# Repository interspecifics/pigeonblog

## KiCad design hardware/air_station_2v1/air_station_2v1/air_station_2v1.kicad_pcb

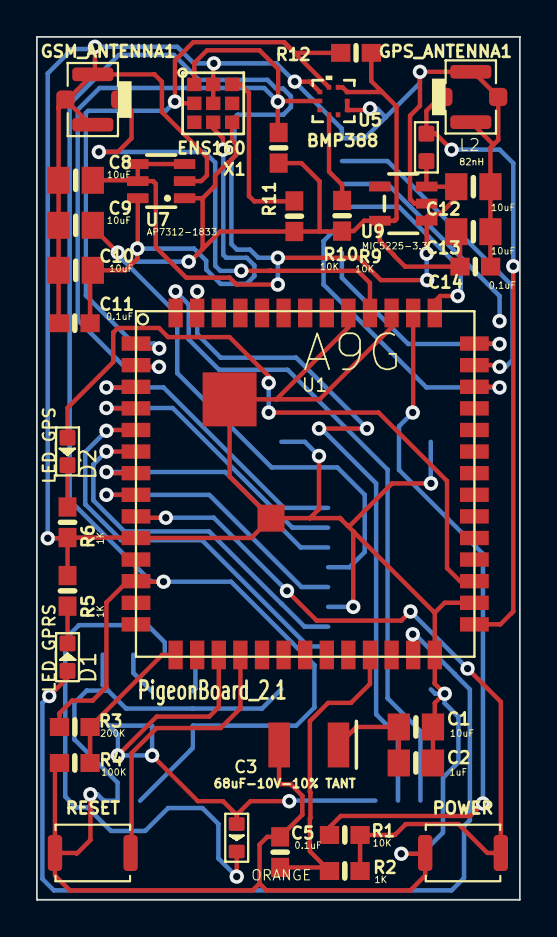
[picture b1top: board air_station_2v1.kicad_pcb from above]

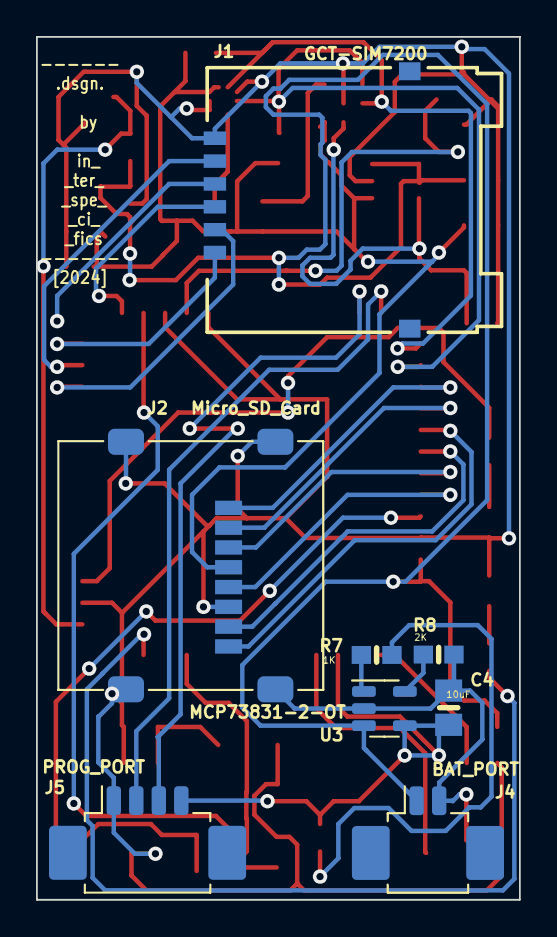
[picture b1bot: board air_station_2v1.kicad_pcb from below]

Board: 2 copper layers, 26.8 x 47.9 mm, 42 parts (8 on the bottom side), 36 nets.

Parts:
C1, C4, C8, C9, C10, C12, C13: 10uF; 0805-NO
C2: 1uF; 0805-NO
C3: 68uF-10V-10% TANT; EIA3528
C5, C11, C14: 0.1uF; 0603-NO
CHG1: ORANGE; D0603
D1: LED_GPRS; LED-0603
D2: LED_GPS; LED-0603
GPS_ANTENNA1: ANTENNA-U-FL; 4P-U-FL
GSM_ANTENNA1: ANTENNA-U-FL; 4P-U-FL
J1: SIM7200-6-0-18-00-X_REVA; GCT_SIM7200-6-0-18-00-X_REVA
J2: Micro_SD_Card; microSD_HC_Molex_47219-2001
J4: BAT_PORT; Molex_PicoBlade_53261-0271_1x02-1MP_P1.25mm_Horizontal
J5: PROG_PORT; Molex_PicoBlade_53261-0471_1x04-1MP_P1.25mm_Horizontal
L2: 82nH; L0603
R1, R9, R10: 10K; 0603-NO
R2, R5, R6, R7: 1K; 0603-NO
R3: 200K; 0603-NO
R4: 100K; 0603-NO
R8: 2K; 0603-NO
R11, R12: 4.7K; 0603-NO
SW_POW1: POWER; SW_Push_SPST_NO_Alps_SKRK
SW_RST1: RESET; SW_Push_SPST_NO_Alps_SKRK
U1: A9G
U3: MCP73831-2-OT; SOT-23-5
U5: BMP388; QFN_BMP388_BOS
U7: AP7312-1833; SOT23-6
U9: MIC5225-3.3; SOT23-5
X1: ENS160

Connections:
1.8V: C10.1, C11.1, U7.6 (VOUT1), X1.4 (VDD)
3.3V: C9.1, C13.1, C14.1, J2.4 (VDD), R9.2, R10.2, R11.2, R12.2, U5.1 (VDDIO), U5.10 (VDD), U7.1 (VOUT2), U9.5 (OUT), X1.5 (VDDIO)
+5V: C4.2, CHG1.+, J5.4, U1.17 (VUSB), U3.4 (V_{DD})
+BATT: C8.1, C12.1, J4.1, L2.2, R3.1, U1.11 (VBAT), U1.12 (VBAT@1), U3.3 (V_{BAT}), U7.3 (EN2), U7.4 (EN1), U7.5 (VIN), U9.1 (IN), U9.3 (EN)
/ADC0: R3.2, R4.1, U1.15 (ADC0)
/GPS_RF: GPS_ANTENNA1.D, L2.1, U1.28 (GPS_RF)
/GSM_RF: GSM_ANTENNA1.D, U1.45 (GPRS_RF)
/I2C2_SCL: R12.1, U1.1 (I2C2_SCL), U5.2 (SCK), X1.2 (SCL/SCK)
/I2C2_SDA: R11.1, U1.2 (I2C2_SDA), U5.4 (SDI), X1.1 (SDA/MOSI)
/IO27: D1.+, U1.26 (IO27)
/IO28: D2.+, U1.30 (IO28)
/IO29: C5.1, R2.1, U1.24 (IO29)
/PWR_KEY: R1.1, R2.2, SW_POW1.1, U1.9 (PWRKEY)
/RESET: SW_RST1.1, U1.18 (RESET)
/SD_CLK: J2.5 (CLK), U1.8 (SD_CLK)
/SD_CMD: J2.3 (CMD), U1.7 (SD_CMD)
/SD_D0: J2.7 (DAT0), U1.6 (SD_D0)
/SD_D1: J2.8 (DAT1), U1.5 (SD_D1)
/SD_D2: J2.2 (DAT3/CD), U1.4 (SD_D2)
/SD_D3: J2.1 (DAT2), U1.3 (SD_D3)
/SIM_CLK: J1.C3 (CLK), U1.41 (SM0_CLK)
/SIM_DATA: J1.C7 (I/O), U1.39 (SM0_DIO)
/SIM_RST: J1.C2 (RST), U1.42 (SM0_RST)
/SIM_VDD: J1.C1 (VCC), U1.40 (VSM0)
/UART_RX: J5.3, U1.53 (UART1_RXD)
/UART_TX: J5.2, U1.54 (UART1_TXD)
/VIN_BAT: C1.2, C2.2, C3.A (+)
/VIO: R1.2, U1.43 (VIO)
GND: C1.1, C2.1, C3.C (-), C4.1, C5.2, C8.2, C9.2, C10.2, C11.2, C12.2, C13.2, C14.2, GPS_ANTENNA1.GND1, GPS_ANTENNA1.GND2, GPS_ANTENNA1.GND3, GSM_ANTENNA1.GND1, GSM_ANTENNA1.GND2, GSM_ANTENNA1.GND3, J1.C5 (GND), J2.6 (VSS), J2.9 (SHIELD), J4.2, J5.1, R4.2, R5.1, R6.1, R8.2, SW_POW1.2, SW_RST1.2, U1.10 (GND), U1.27 (GND@1), U1.29 (GND@2), U1.44 (GND@3), U1.46 (GND@4), U1.55 (GND@5), U1.56 (GND@6), U3.2 (V_{SS}), U5.3 (VSS), U5.8 (VSS), U5.9 (VSS), U7.2 (GND), U9.2 (GND), X1.8 (GND), X1.9 (GND)
unnamed: CHG1.-, R7.1
unnamed: D1.-, R5.2
unnamed: D2.-, R6.2
unnamed: R8.1, U3.5 (PROG)
unnamed: R7.2, U3.1 (STAT)
unnamed: R9.1, U5.6 (CSB)
unnamed: R10.1, X1.7 (~CS)

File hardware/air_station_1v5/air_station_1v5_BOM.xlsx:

|  |  | PigeonBoard v2.0 | Bill of Materials
 |  |  | by Interspecifics | 2023.10.19
Item # | Designator | Qty | Manufacturer | MFR.Part # | Description | Footprint | TYPE |  | Value | Cmp name | JLCPCB Part # | Datasheet
1 | C1, C4, C12, C13 | 4 | TDK | CGA4J1X5R1C106KT0Y0E | 16V 10uF X5R ±10% 0805 Multilayer Ceramic Capacitors MLCC - SMD/SMT ROHS | 0805-NO | SMD |  | 10uF | CAP_CERAMIC0805-NOOUTLINE | C342712 | https://datasheet.lcsc.com/lcsc/2304140030_TDK-CGA4J1X5R1C10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
2 | C2 | 1 | Vishay Intertech | VJ0805Y105KXQTW1BC | 10V 1uF X7R ±10% 0805 Multilayer Ceramic Capacitors MLCC - SMD/SMT ROHS | 0805-NO | SMD |  | 1uF | CAP_CERAMIC0805-NOOUTLINE | C511417 | https://datasheet.lcsc.com/lcsc/2005201835_Vishay-Intertech-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
3 | C3 | 1 | KEMET | T491B686K006AT | 68uF 10V 1.4Ω@100kHz ±20% CASE-B-3528 Tantalum Capacitors ROHS | EIA3528 | SMD |  | 68uF-POLAR-EIA3528-10V-10%(TANT) | 68UF-POLAR-EIA3528-10V-10%(TANT) | C122284 | https://datasheet.lcsc.com/lcsc/2304140030_KEMET-T491B686K00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
4 | C5,C14 | 2 | Samsung Electro-Mechanics | CL10C101JC8NNNC | 100V 100pF C0G ±5% 0603 Multilayer Ceramic Capacitors MLCC - SMD/SMT ROHS | 0603-NO | SMD |  | 0.1uF | CAP_CERAMIC0603_NO | C296717 | https://datasheet.lcsc.com/lcsc/2304140030_Samsung-Electro-M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
5 | C8, C9, C10 | 3 | TDK | CGA4J1X5R1C106KT0Y0E | 16V 10uF X5R ±10% 0805 Multilayer Ceramic Capacitors MLCC - SMD/SMT ROHS | 0805-NO | SMD |  | 10uF | CAP_CERAMIC0805-NOOUTLINE | C342712 | https://datasheet.lcsc.com/lcsc/2304140030_TDK-CGA4J1X5R1C10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
6 | C11 | 1 | Samsung Electro-Mechanics | CL10C101JC8NNNC | 100V 100pF C0G ±5% 0603 Multilayer Ceramic Capacitors MLCC - SMD/SMT ROHS | 0603-NO | SMD |  | 0.1uF | CAP_CERAMIC0603_NO | C296717 | https://datasheet.lcsc.com/lcsc/2304140030_Samsung-Electro-M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
7 | CHG1 | 1 | Amicc | A-SP192YY3C-A01-4T | 180mcd Colorless transparence -40℃~+85℃ 585.5nm~594.5nm yellow 120° 60mW 0603 L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 | LED-0603 | SMD |  | ORANGE | 007-LED0603 | C5151485 | https://datasheet.lcsc.com/lcsc/2209161630_Amicc-A-SP192YY3C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
8 | D1 | 1 | Amicc | A-SP192YB1C-A01-4T | 360mcd Colorless transparence -40℃~+85℃ 465nm~475nm blue 120° 60mW 0603 Light E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 | LED-0603 | SMD |  | LED_GPRS | LED'0603' | C5151484 | https://datasheet.lcsc.com/lcsc/2209161630_Amicc-A-SP192YB1C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
9 | D2 | 1 | Amicc | A-SP192YB1C-A01-4T | 360mcd Colorless transparence -40℃~+85℃ 465nm~475nm blue 120° 60mW 0603 Light E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 | LED-0603 | SMD |  | LED_GPS | LED'0603' | C5151484 | https://datasheet.lcsc.com/lcsc/2209161630_Amicc-A-SP192YB1C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
10 | GPS_ANTENNA1, GSM_ANTENNA1 | 2 | Shenzhen Kinghelm Elec | KH-IPEX3-2020 | 1 Inner needle IPEX Board Edge 6GHz 1.4mm SMD RF Connectors / Coaxial Connector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 | IPEX RF SMD | SMD |  | ANTENNA-U-FL | ANTENNA-U-FL | C530665 | https://datasheet.lcsc.com/lcsc/2005121133_Shenzhen-Kinghelm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
12 | J1 | 1 | Hanbo Electronic | SMO-1545 | SIM Card Connectors Clamshell Gold plating 1.8mm Deck ROHS | GCT_SIM7200 | SMD |  | SIM7200-6-0-18-00-X_REVA | SIM7200-6-0-18-00-X_REVA | C410354 | https://datasheet.lcsc.com/lcsc/2211111000_Hanbo-Electronic-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
13 | J2 | 1 | XKB Connectivity | XKTF-1307-16 | MicroSD SD Card Connectors SMD, 1.6mm Gold plating Deck Copper Alloy Clamshell 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 | Molex_47219-2001 | SMD |  | Micro_SD_Card | Micro_SD_Card | C2885067 | https://datasheet.lcsc.com/lcsc/2110120730_XKB-Connectivity-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
14 | L2 | 1 | Murata Electronics | LQG18HN82NJ00D | 350mA 82nH ±5% 850mΩ 0603 Inductors (SMD) ROHS | L0603 | SMD |  | 82nH | L'0603' | C98008 | https://datasheet.lcsc.com/lcsc/1810311140_Murata-Electronic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
15 | R1, R9, R10 | 3 | ROHM Semicon | ESR03EZPF1002 | 250mW Thick Film Resistors ±100ppm/℃ ±1% 10kΩ 0603 Chip Resistor - Surface Moun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 | 0603-NO | SMD |  | 10K | RESISTOR_0603_NOOUT | C510087 | https://datasheet.lcsc.com/lcsc/2304140030_ROHM-Semicon-ESR0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
16 | R2, R5, R6, R7 | 4 | PANASONIC | ERJUP3F1001V | 250mW Thick Film Resistors ±100ppm/℃ ±1% 1kΩ 0603 Chip Resistor - Surface Mount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 | 0603-NO | SMD |  | 1K | RESISTOR_0603_NOOUT | C491209 | https://datasheet.lcsc.com/lcsc/2005291533_PANASONIC-ERJUP3F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
17 | R3 | 1 | PANASONIC | ERJPA3J204V | 250mW Thick Film Resistors ±5% ±200ppm/℃ 200kΩ 0603 Chip Resistor - Surface Mou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 | 0603-NO | SMD |  | 200K | RESISTOR_0603_NOOUT | C445854 | https://datasheet.lcsc.com/lcsc/2304140030_PANASONIC-ERJPA3J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
18 | R4 | 1 | PANASONIC | ERJUP3F1003V | 250mW Thick Film Resistors ±100ppm/℃ ±1% 100kΩ 0603 Chip Resistor - Surface Mou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 | 0603-NO | SMD |  | 100K | RESISTOR_0603_NOOUT | C491213 | https://datasheet.lcsc.com/lcsc/2005291533_PANASONIC-ERJUP3F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
19 | R8 | 1 | PANASONIC | ERJPA3J202V | 250mW Thick Film Resistors ±5% ±200ppm/℃ 2kΩ 0603 Chip Resistor - Surface Mount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 | 0603-NO | SMD |  | 2K | RESISTOR_0603_NOOUT | C445827 | https://datasheet.lcsc.com/lcsc/2304140030_PANASONIC-ERJPA3J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
20 | SW_POW1 | 1 | ALPSALPINE | SKRKAGE020 | 50mA Brick nogging SPST 12V SMD,2.9x3.9mm Tactile Switches ROHS | SMD,2.9x3.9mm | SMD |  | POWER | SW_Push | C262416 | https://datasheet.lcsc.com/lcsc/1808101152_ALPSALPINE-SKRKAG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
21 | SW_RST1 | 1 | ALPSALPINE | SKRKAGE020 | 50mA Brick nogging SPST 12V SMD,2.9x3.9mm Tactile Switches ROHS | SMD,2.9x3.9mm | SMD |  | RESET | SW_Push | C262416 | https://datasheet.lcsc.com/lcsc/1808101152_ALPSALPINE-SKRKAG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
22 | U1 | 1 | Ai-Thinker | A9G | A9G GPRS/GSM+GPS/BDS Module | AG, SMD, 18.8x19.2mm | SMD |  | A9G | A9G | C133738 | https://docs.ai-thinker.com/_media/b101ps01a4_a9g_product_sp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 |  | https://www.aliexpress.com/item/1005005406907721.html?spm=a2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
23 | U3 | 1 | Microchip Tech | MCP73831T-2ATI/OT | Single cell, Li-Ion/Li-Po charge management controller, 4.20V, Tri-State Status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 | SOT23-5 | SMD |  | MCP73831-2-OT | MCP73831-2-OT | C14879 | https://datasheet.lcsc.com/lcsc/2304140030_Microchip-Tech-MC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
24 | U5 | 1 | Bosch Sensortec | BMP388 | Digital pressure Sensor | QFN_BMP388_BOS | BGA/QFP |  | BMP388 | BMP388 | C779278 | https://www.bosch-sensortec.com/media/boschsensortec/downloa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
25 | U7 | 1 | Diodes Incorporated | AP7312-1833W6-7 | LDO Voltage Regulators Dual 150mA LDO Reg 60uA 1.8 to 3.3 65dB | SOT23-6 | SMD |  | AP7312-1833 | VREG_SOT23-6_DUALAP7312 | C195066 | https://datasheet.lcsc.com/lcsc/1810190047_Diodes-Incorporat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
26 | U9 | 1 | Microchip Tech | MIC5225-3.3YM5-TR | LDO Voltage Regulators High Vin, Low Iq Regulator 3.3 V | SOT23-5 | SMD |  | MIC5225-3.3 | VREG_SOT23-5 | C512101 | https://datasheet.lcsc.com/lcsc/2004302108_Microchip-Tech-MI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
27 | X1 | 1 | Sciosense | ENS160-BGLR | Digital Metal Oxide Multi-Gas Sensor | ENS160 | BGA/QFP |  | ENS160 | ENS160 | C3659351 | https://www.sciosense.com/wp-content/uploads/documents/SC-00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
28 | J4 | 1 | MOLEX | 532610271 | 1x2P 1 1.25mm 2 bronze SMD,P=1.25mm Wire To Board / Wire To Wire Connector ROHS | Molex_PicoBlade_53261-0271_1x02-1MP_P1.25mm_Horizontal | SMD |  | BAT_PORT | Conn_01x02 | C189700 | https://datasheet.lcsc.com/lcsc/2304140030_MOLEX-532610271_C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
29 | J5 | 1 | MOLEX | 532610471 | 1x4P 1 1.25mm 4 bronze SMD,P=1.25mm Wire To Board / Wire To Wire Connector ROHS | Molex_PicoBlade_53261-0471_1x04-1MP_P1.25mm_Horizontal | SMD |  | PROG_PORT | Conn_01x04 | C240847 | https://datasheet.lcsc.com/lcsc/2304140030_MOLEX-532610471_C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

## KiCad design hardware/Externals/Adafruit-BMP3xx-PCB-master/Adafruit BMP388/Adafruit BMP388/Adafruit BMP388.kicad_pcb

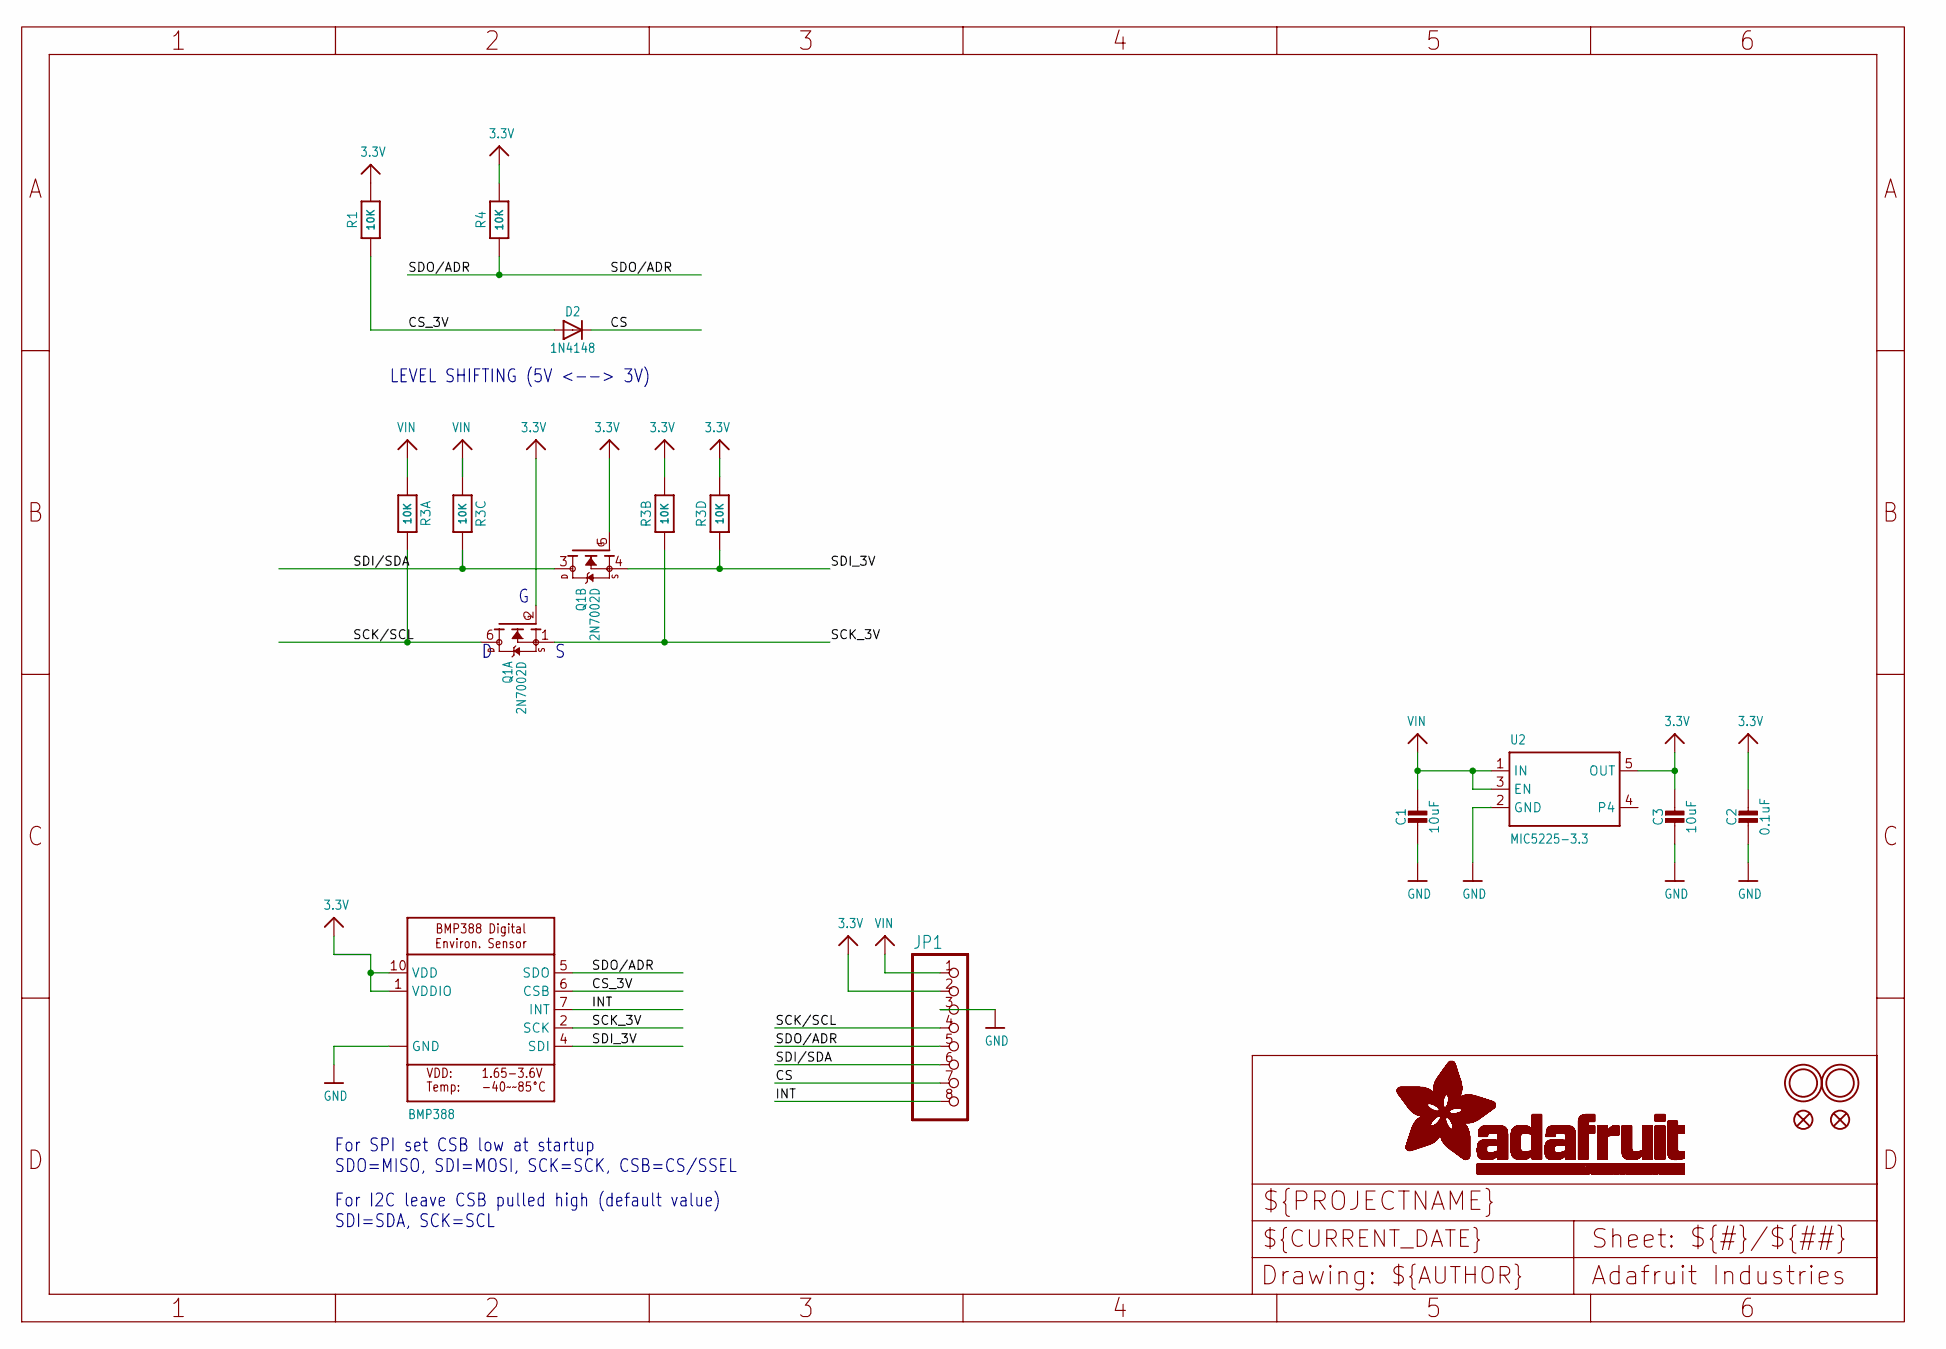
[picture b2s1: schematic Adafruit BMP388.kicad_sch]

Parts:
C1, C3: 10uF; 0805-NO
C2: 0.1uF; 0603-NO
D2: 1N4148; SOD-323
IC1: BMP388
JP1: HEADER-1X870MIL; 1X08_ROUND_70
Q1: 2N7002D; SOT363
R1, R4: 10K; 0603-NO
R3: 10K; RESPACK_4X0603
U2: MIC5225-3.3; SOT23-5
U$5, U$15: FIDUCIAL_1MM
U$7, U$8: MOUNTINGHOLE2.0; MOUNTINGHOLE_2.0_PLATED

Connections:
3.3V: C2.1, C3.1, IC1.1 (VDDIO), IC1.10 (VDD), JP1.2, Q1.2 (G), Q1.5 (G), R1.2, R3.2 (1), R3.4 (1), R4.2, U2.5 (OUT)
CS: D2.C, JP1.7
CS_3V: D2.A, IC1.6 (CSB), R1.1
GND: C1.2, C2.2, C3.2, IC1.3 (GND), IC1.8 (GND), IC1.9 (GND), JP1.3, U2.2 (GND)
INT: IC1.7 (INT), JP1.8
SCK/SCL: JP1.4, Q1.6 (D), R3.8 (2)
SCK_3V: IC1.2 (SCK), Q1.1 (S), R3.7 (2)
SDI/SDA: JP1.6, Q1.3 (D), R3.6 (2)
SDI_3V: IC1.4 (SDI), Q1.4 (S), R3.5 (2)
SDO/ADR: IC1.5 (SDO), JP1.5, R4.1
VIN: C1.1, JP1.1, R3.1, R3.3 (1), U2.1 (IN), U2.3 (EN)

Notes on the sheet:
For SPI set CSB low at startup SDO=MISO, SDI=MOSI, SCK=SCK, CSB=CS/SSEL
LEVEL SHIFTING (5V <--> 3V)
For I2C leave CSB pulled high (default value) SDI=SDA, SCK=SCL

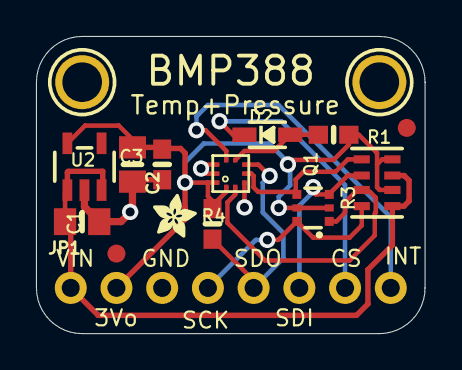
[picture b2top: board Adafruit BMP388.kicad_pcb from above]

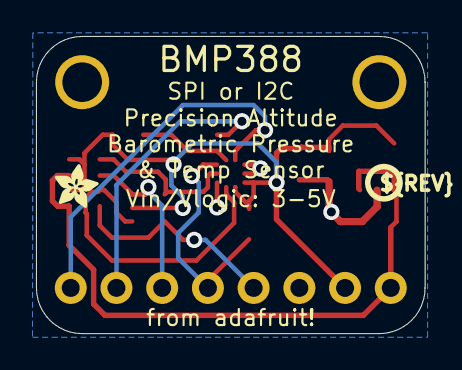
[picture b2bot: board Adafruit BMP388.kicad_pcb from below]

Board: 2 copper layers, 21.6 x 16.5 mm, 18 parts (2 on the bottom side), 11 nets.

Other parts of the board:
U$2, U$6: ADAFRUIT_2.5MM
U$20: PCBFEAT-REV-040

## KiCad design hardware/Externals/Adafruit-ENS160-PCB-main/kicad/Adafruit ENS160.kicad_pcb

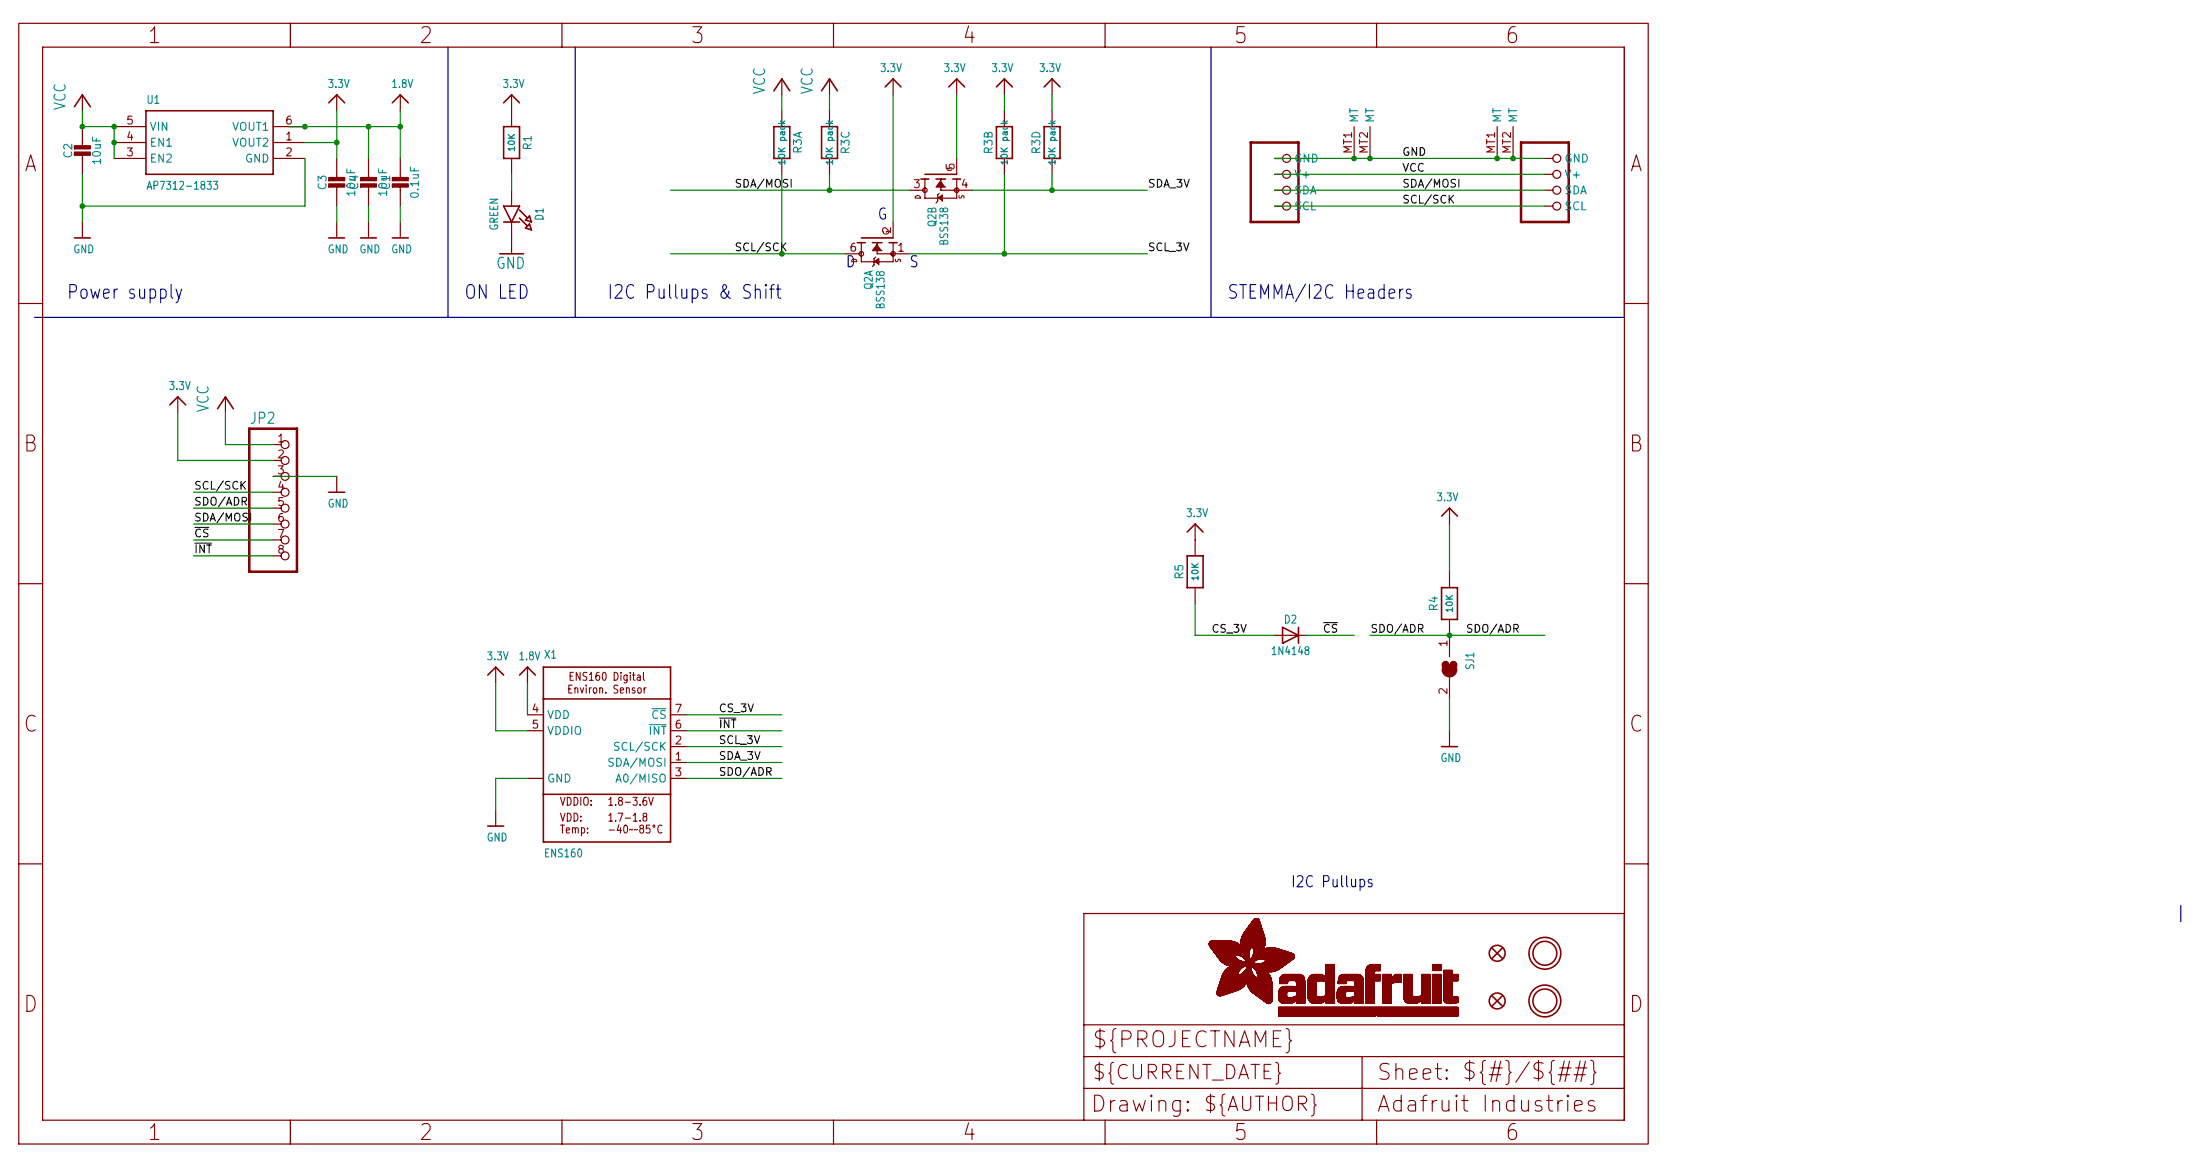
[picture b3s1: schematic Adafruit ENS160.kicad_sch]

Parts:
C1: 0.1uF; 0603-NO
C2, C3, C4: 10uF; 0805-NO
CONN3, CONN4: STEMMA_I2C_QT; JST_SH4
D1: GREEN; CHIPLED_0603_NOOUTLINE
D2: 1N4148; SOD-323
FID3, FID4: FIDUCIAL_1MM
JP2: HEADER-1X870MIL; 1X08_ROUND_70
Q2: BSS138; SOT363
R1, R4, R5: 10K; 0603-NO
R3: 10K pack; RESPACK_4X0603
SJ1: SOLDERJUMPER; SOLDERJUMPER_ARROW_NOPASTE
U1: AP7312-1833; SOT23-6
U$1, U$17: MOUNTINGHOLE2.5; MOUNTINGHOLE_2.5_PLATED
X1: ENS160

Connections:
1.8V: C1.1, C4.1, U1.6 (VOUT1), X1.4 (VDD)
3.3V: C3.1, JP2.2, Q2.2 (G), Q2.5 (G), R1.1, R3.2 (1), R3.4 (1), R4.2, R5.2, U1.1 (VOUT2), X1.5 (VDDIO)
CS_3V: D2.A, R5.1, X1.7 (~CS)
GND: C1.2, C2.2, C3.2, C4.2, CONN3.1 (GND), CONN3.MT1 (MT), CONN3.MT2 (MT), CONN4.1 (GND), CONN4.MT1 (MT), CONN4.MT2 (MT), D1.C, JP2.3, SJ1.2, U1.2 (GND), X1.8 (GND), X1.9 (GND)
unnamed: D1.A, R1.2
SCL/SCK: CONN3.4 (SCL), CONN4.4 (SCL), JP2.4, Q2.6 (D), R3.8 (2)
SCL_3V: Q2.1 (S), R3.7 (2), X1.2 (SCL/SCK)
SDA/MOSI: CONN3.3 (SDA), CONN4.3 (SDA), JP2.6, Q2.3 (D), R3.6 (2)
SDA_3V: Q2.4 (S), R3.5 (2), X1.1 (SDA/MOSI)
SDO/ADR: JP2.5, R4.1, SJ1.1, X1.3 (A0/MISO)
VCC: C2.1, CONN3.2 (V+), CONN4.2 (V+), JP2.1, R3.1, R3.3 (1), U1.3 (EN2), U1.4 (EN1), U1.5 (VIN)
~CS: D2.C, JP2.7
~INT: JP2.8, X1.6 (~INT)

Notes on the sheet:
STEMMA/I2C Headers
I2C Pullups & Shift
I2C Pullups
ON LED
Power supply

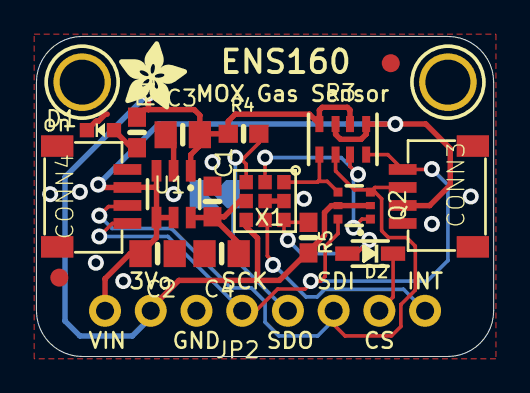
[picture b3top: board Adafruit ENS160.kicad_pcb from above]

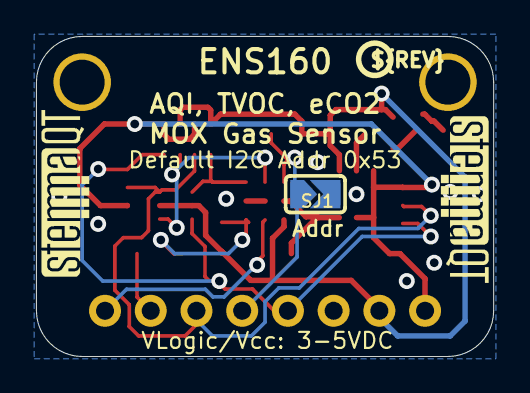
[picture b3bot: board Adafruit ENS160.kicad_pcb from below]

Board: 2 copper layers, 25.4 x 17.8 mm, 25 parts (4 on the bottom side), 13 nets.

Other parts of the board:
U$20: ADAFRUIT_3.5MM
U$25: PCBFEAT-REV-040
U$30, U$31: STEMMAQT

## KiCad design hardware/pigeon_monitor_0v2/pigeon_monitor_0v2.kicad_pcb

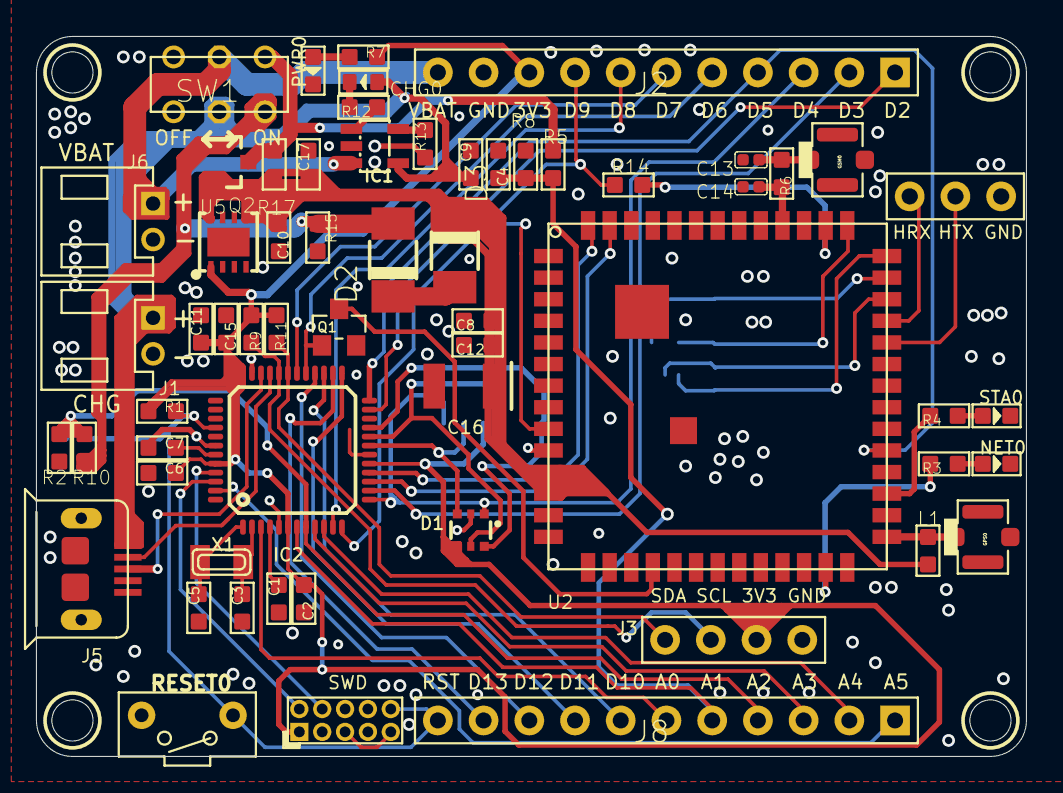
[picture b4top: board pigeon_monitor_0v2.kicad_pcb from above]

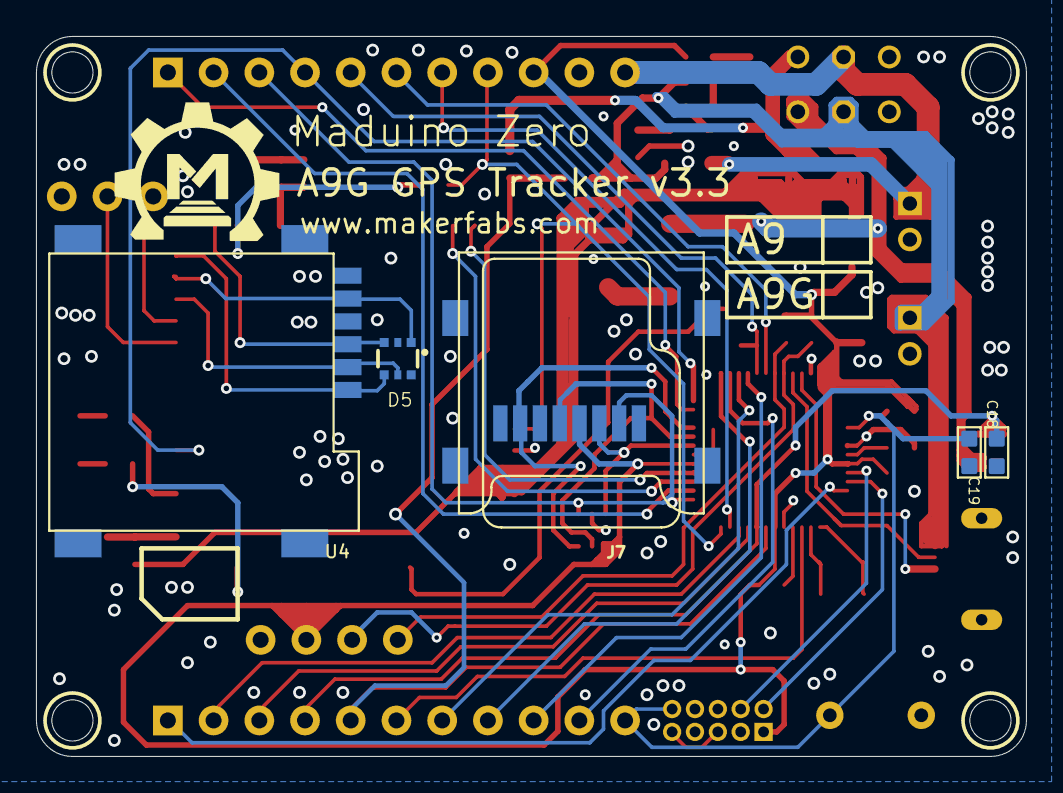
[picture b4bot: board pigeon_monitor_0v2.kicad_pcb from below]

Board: 2 copper layers, 55.0 x 40.0 mm, 66 parts (6 on the bottom side), 61 nets.

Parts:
C1, C7, C12: 1uF; C0603
C2, C6, C15: 100nF; C0603
C3, C5: 22pF; C0603
C4, C18, C19: 0.1uF; C0603
C8, C17: 10uF; C0603
C9: 10u; C0603
C10, C11: 4.7uF; C0603
C13, C14: NC; C0402
C16: 100uF; EIA3528
CHG0: ORANGE; D0603
CN2: PINHEAD-2x5-P1.27; PINHEAD_2X05_127
D1, D5: SMF05C; SOT363
D2: S2M; DO-214AC
D3: SS34; DO-214AC
GPS0: 4P-U-FL
GSM0: 4P-U-FL
IC1: MCP73831/OT; SOT23-5L
IC2: SAMD21G18A-AUT; TQFP48-7X7
J1, J6: PH2.0-2P-90-DIP
J2, J8: 11P-2.54
J3: 4P-65_35ROUND
J4: 3P-2.54
J5: USB-MICRO-5P; MICRO-USB-5P
J7: 8P-SMD
L1: 82nH; L0603
NET0: Blue; LED-0603
PWR0: RED; LED-0603
Q1: BSN20; SOT23@1
Q2: MOSFET-PCHANNEL; SOT23-3
R1, R14: 10k; R0603
R2, R10: 1M; R0603
R3, R4: 330R; R0603
R5, R8: 1M/1%; R0603
R6: 0R; R0603
R7: 1K; R0603
R9, R11: 4.7K; R0603
R12: 1k; R0603
R13: 2k; R0603
R15: 100k; R0603
R17: NC; R0603
RESET0: 2P-7.62X3.56-90D
STA0: green; LED-0603
SW1: 6P-2CH-2.54-7.6X3.0
U2: A9G
U4: MICROSIM
U5: AP7361C-33FGE; 8-UDFN
U$1: MAKERFABS_0.3
X1: 32.768; XTAL3215

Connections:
+3V3: C2.2, C6.1, C11.2, C15.1, CN2.1, D1.4, IC2.6, IC2.17, IC2.36, IC2.44, J2.9, J3.3, J7.4, R1.2, R7.1, R9.2, R11.2, U5.1
A0: IC2.3, J8.6
A1: C4.1, IC2.7, J8.5, R5.1, R8.2
A2: C18.1, IC2.8, J8.4, R2.2, R10.1
A3: IC2.9, J8.3
A4: IC2.10, J8.2
A5: IC2.47, J8.1
AREFA: C1.1, IC2.4
D0: IC2.16, U2.54
D1: IC2.15, U2.53
D2: IC2.23, J2.1
D3: IC2.14, J2.2
D4: D1.1, IC2.13, J2.3, J7.2
D5: IC2.24, J2.4, U2.32
D6: IC2.29, J2.5, Q1.1
D7: IC2.30, J2.6
D8: IC2.11, J2.7
D9: IC2.12, J2.8, R14.1, U2.9
D10: IC2.27, J8.7
D11: IC2.25, J8.8
D12: IC2.28, J8.9
D13: IC2.26, J8.10
D+: IC2.34, J5.3
D-: IC2.33, J5.2
GND: C1.2, C2.1, C3.2, C4.2, C5.2, C6.2, C7.2, C8.1, C9.1, C10.1, C11.1, C12.1, C13.1, C14.1, C15.2, C16.C, C17.1, C18.2, C19.1, CN2.3, CN2.5, CN2.9, D1.2, D5.2, GPS0.GND1, GPS0.GND2, GPS0.GND3, GSM0.GND1, GSM0.GND2, GSM0.GND3, IC1.2, IC2.5, IC2.18, IC2.35, IC2.42, J1.2, J2.10, J3.4, J4.3, J5.5, J5.E1, J5.E2, J5.P1, J5.P2, J6.2, J7.6, J7.9, J7.10, J7.11, J7.12, NET0.-, PWR0.-, Q1.2, R2.1, R8.1, R13.2, R15.2, RESET0.P$2, STA0.-, U2.10, U2.27, U2.29, U2.44, U2.46, U2.55, U2.56, U4.5, U5.4, U5.EP
GPS_RF: GPS0.D, L1.1, U2.28
GSM_RF: C14.2, R6.1, U2.45
HRXD: J4.1, U2.38
HTXD: J4.2, U2.37
IO27: R3.1, U2.26
IO28: R4.1, U2.30
MISO: D1.6, IC2.21, J7.7
MOSI: D1.3, IC2.19, J7.3
unnamed: R4.2, STA0.+
unnamed: D2.C, D3.A
unnamed: PWR0.+, R7.2
unnamed: NET0.+, R3.2
unnamed: Q1.3, U2.18
unnamed: CHG0.-, R12.1
unnamed: IC1.1, R12.2
unnamed: IC1.5, R13.1
unnamed: C13.2, GSM0.D, R6.2
PA00_XIN32: C5.1, IC2.1, X1.P$2
PA01_XOUT32: C3.1, IC2.2, X1.P$1
RESET: C19.2, CN2.10, IC2.40, J8.11, R1.1, RESET0.P$1
SCK: D1.5, IC2.20, J7.5
SCL: IC2.32, J3.2, R9.1
SDA: IC2.31, J3.1, R11.1
SIM_CLK: D5.4, U2.41, U4.3
SIM_DATA: D5.5, U2.39, U4.7
SIM_RST: D5.3, U2.42, U4.2
SIM_VDD: D5.1, U2.40, U4.1
SWCLK: CN2.4, IC2.45
SWDIO: CN2.2, IC2.46
VBAT: IC1.3, J2.11, J6.1, SW1.COM1
VBAT_IN: Q2.3, R5.2, R17.1, SW1.CH1A
VBUS: C9.2, CHG0.+, IC1.4, J1.1, J5.1, SW1.COM2
VDDCORE: C7.1, IC2.43
VIN: C8.2, C10.2, C12.2, C16.A, C17.2, D3.C, L1.2, Q2.2, R17.2, U2.11, U2.12, U5.5, U5.8
VIO: R14.2, U2.43
VSYS: D2.A, Q2.1, R10.2, R15.1, SW1.CH2A

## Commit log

2023-08-04 Pigeon Blog Reprise
    Base Hardware + Firmware
2023-08-08 v0.3
    send unformated POST requests
2023-08-08 adds notebook to test backend requests
2023-08-08 initial db rules
2023-08-09 more relaxed db rules
2023-08-09 Create pidgeon_track_0v4.py
    better energy management around gprs for battery operation
2023-08-11 added POST support A9G->Firebase
    added POST support A9G->Firebase
2023-08-11 Aadded POST support A9G->Firebase
    added POST support A9G->Firebase
2023-08-12 updates rules for A9G posts
2023-08-14 adjust database rules
2023-08-15 adds vs codespace pattern to gitignore
2023-08-15 Adds github workflow to build/deploy frontend on pushes to frontend/ directory
2023-08-15 initial sveltekit app commit
2023-08-15 fix working directory in workflows/deploy-frontend.yml
2023-08-15 trigger build
2023-08-15 fix working directory in workflows/deploy-frontend again
2023-08-15 trigger action when action file is pushed
2023-08-15 remove frontend. moved to own repo
2023-08-16 adds rules for /sessions/ section of db
2023-08-16 test code for seeding /sessions/ section of db
2023-08-16 simplify date manipulation math
2023-08-18 adjusts lat,lon range and changes time between posts in backend test script
2023-08-18 adds cell to remove records from db. use gaussian for lat/lon not uniform
2023-08-21 remove stale cells for 'seeding' sessions/ section of db; been moved to JS in frontend
2023-08-21 new db rules for sessions/ section
2023-08-21 adds cell to py nb to delete specific days of data
2023-08-22 adjust LAT/LON. individual LAT/LON for each pigeon. better delete logic. date to unix time util.
2023-08-29 Create pidgeon_track_0v6.py
    gps management
2023-09-05 adjust max LAT
2023-09-15 update rules. adds new data format to test notebook
2024-02-12 pigeon_board_2.0
    system design project for pigeonboard2.0
2024-02-13 Add adafruit schematics
2024-02-20 adds new sensors
2024-02-25 use realistic sensor values
2024-02-25 update firebase test notebook
2024-03-02 adjust cropmap function
2024-03-02 adds helpers to read raw sensor and calculate ppm of other gases
2024-03-03 adds path test data to backenbd notebook
2024-04-15 update 1.9
    I2C pullups update
2024-04-23 update 2v1
    >added R11, R12 pull up resistors
    >added A0 missing track
    >maximize gnd bus coverage
    >
2024-10-19 Update main.py
    public
2024-11-16 workshop version
2024-11-16 workshop update
